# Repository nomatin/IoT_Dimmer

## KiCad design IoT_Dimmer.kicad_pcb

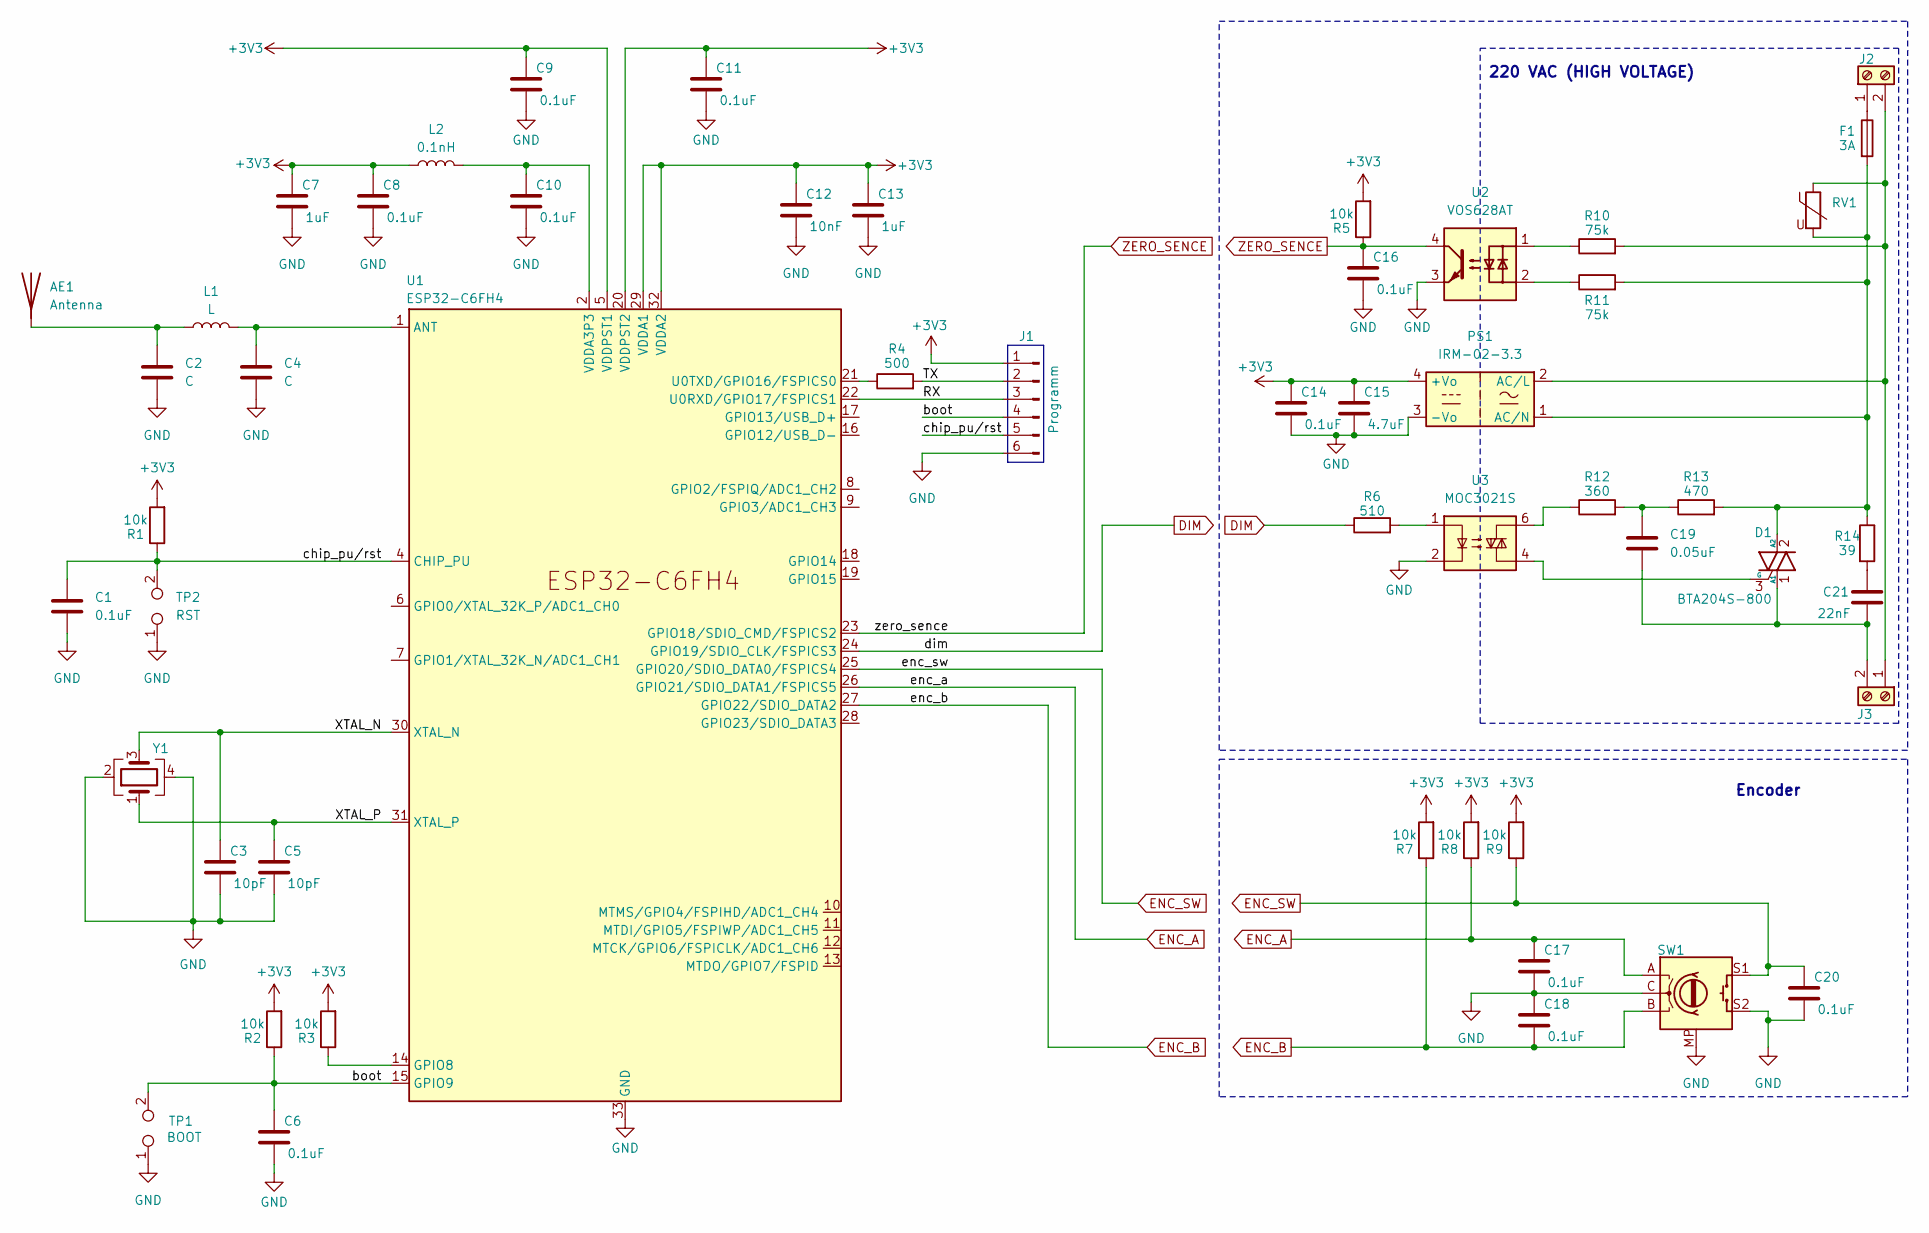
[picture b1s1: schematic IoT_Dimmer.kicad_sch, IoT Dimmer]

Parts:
AE1: Antenna; Molex_47948-0001_2.4Ghz
C1, C6, C8, C9, C10, C11, C14, C16, C17, C18, C20: 0.1uF; C_0603_1608Metric
C2, C4: C; C_0402_1005Metric
C3, C5: 10pF; C_0603_1608Metric
C7, C13: 1uF; C_0603_1608Metric
C12: 10nF; C_0603_1608Metric
C15: 4.7uF; C_0603_1608Metric
C19: 0.05uF; C_1812_4532Metric
C21: 22nF; C_1812_4532Metric
D1: BTA204S-800; TO-252-3_TabPin2
F1: 3A; Fuse_Littelfuse-NANO2-462
J1: Conn_01x06_Pin
J2: Screw_Terminal_01x02; CONN2_2059-302&slash_998-403_WAG
J3: Wago_2059-302998-403:CONN2_2059-302&slash_998-403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
L1: L; L_0402_1005Metric
L2: 0.1nH; L_0603_1608Metric
PS1: IRM-02-3.3; Converter_ACDC_MeanWell_IRM-02-xx_THT
R1, R2, R3, R5, R7, R8, R9: 10k; R_0603_1608Metric
R4: 500; R_0603_1608Metric
R6: 510; R_0603_1608Metric
R10, R11: 75k; R_1206_3216Metric
R12: 360; R_1206_3216Metric
R13: 470; R_1206_3216Metric
R14: 39; R_1206_3216Metric
RV1: Varistor; RV_Disc_D7mm_W3.4mm_P5mm
SW1: EVE-SBBFE516B
TP1: BOOT; TestPoint_Bridge_Pitch2.0mm_Drill0.7mm
TP2: RST; TestPoint_Bridge_Pitch2.0mm_Drill0.7mm
U1: ESP32-C6FH4; QFN-32-1EP_5x5mm_P0.5mm_EP3.6x3.6mm
U2: VOS628AT; SOIC127P700X210-4N
U3: MOC3021S; DIP6_SMD
Y1: Crystal_GND24; Crystal_SMD_2016-4Pin_2.0x1.6mm

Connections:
+3V3: C7.1, C8.1, C9.1, C11.1, C12.1, C13.1, C14.1, C15.1, J1.1, L2.1, PS1.4 (+Vo), R1.2, R2.2, R3.2, R5.2, R7.2, R8.2, R9.2, U1.5 (VDDPST1), U1.20 (VDDPST2), U1.29 (VDDA1), U1.32 (VDDA2)
/RX: J1.3, U1.22 (U0RXD/GPIO17/FSPICS1)
/TX: J1.2, R4.2
/XTAL_N: C3.1, U1.30 (XTAL_N), Y1.3
/XTAL_P: C5.1, U1.31 (XTAL_P), Y1.1
/boot: C6.1, J1.4, R2.1, TP1.2, U1.15 (GPIO9)
/chip_pu/rst: C1.1, J1.5, R1.1, TP2.2, U1.4 (CHIP_PU)
DIM: R6.1, U1.24 (GPIO19/SDIO_CLK/FSPICS3)
ENC_A: C17.1, R8.1, SW1.A, U1.26 (GPIO21/SDIO_DATA1/FSPICS5)
ENC_B: C18.2, R7.1, SW1.B, U1.27 (GPIO22/SDIO_DATA2)
ENC_SW: C20.1, R9.1, SW1.S1, U1.25 (GPIO20/SDIO_DATA0/FSPICS4)
GND: C1.2, C2.2, C3.2, C4.2, C5.2, C6.2, C7.2, C8.2, C9.2, C10.2, C11.2, C12.2, C13.2, C14.2, C15.2, C16.2, C17.2, C18.1, C20.2, J1.6, PS1.3 (-Vo), SW1.C, SW1.MP, SW1.S2, TP1.1, TP2.1, U1.33 (GND), U2.3, U3.2, Y1.2, Y1.4
unnamed: AE1.1 (A), C2.1, L1.1
unnamed: C10.1, L2.2, U1.2 (VDDA3P3), U1.3 (VDDA3P3)
unnamed: C19.1, R12.2, R13.1
unnamed: C21.1, R14.2
unnamed: C19.2, C21.2, D1.1 (A1), J3.2
unnamed: D1.2 (A2), F1.2, PS1.1 (AC/N), R11.2, R13.2, R14.1, RV1.2
unnamed: D1.3 (G), U3.4
unnamed: F1.1, J2.1
unnamed: J2.2, J3.1, PS1.2 (AC/L), R10.2, RV1.1
unnamed: R6.2, U3.1
unnamed: R10.1, U2.1
unnamed: R11.1, U2.2
unnamed: R12.1, U3.6
unnamed: C4.1, L1.2, U1.1 (ANT)
unnamed: R3.1, U1.14 (GPIO8)
unnamed: R4.1, U1.21 (U0TXD/GPIO16/FSPICS0)
ZERO_SENCE: C16.1, R5.1, U1.23 (GPIO18/SDIO_CMD/FSPICS2), U2.4

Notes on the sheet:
220 VAC (HIGH VOLTAGE)
Encoder

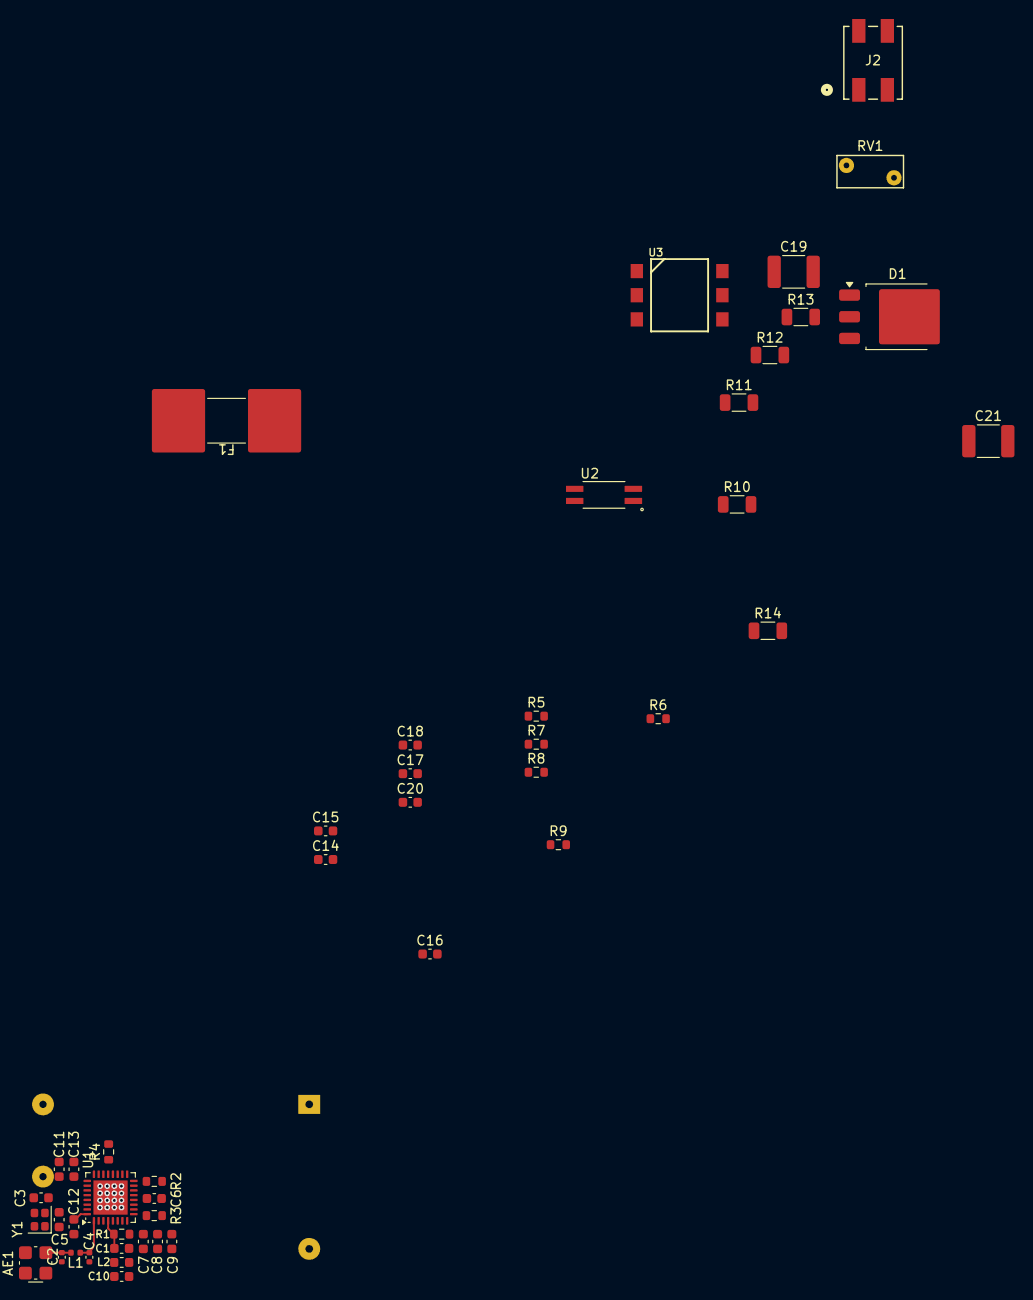
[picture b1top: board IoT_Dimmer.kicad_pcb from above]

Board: 4 copper layers, 47 parts (1 on the bottom side), 27 nets.

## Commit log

2026-03-31 gitignore
2026-03-31 Add README
2026-04-01 add lib
2026-04-01 CPU and 220
2026-04-02 Power esp32
2026-04-02 beta sheet
2026-04-03 PCB_start
2026-04-09 CPU_STAND
